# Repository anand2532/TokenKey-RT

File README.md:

# TokenKey RT

TokenKey RT is a compact USB-C desktop/laptop accessory built on the NXP i.MX RT1062 (Cortex-M7, up to 600 MHz; MIMXRT1062DVL6B, 10x10 mm BGA). It accelerates AI token-usage optimization — context reduction, request analysis and cost monitoring — working together with a Linux companion application on the host laptop.

## Repository layout

| Path | Contents |
|------|----------|
| `docs/` | Specifications, design decisions and project documentation |
| `docs/poc/` | Proof-of-concept and product-value analyses (TokenKey PoC bot; used by TokenKey PM) |
| `hardware/schematic/` | Whole KiCad project: `TokenKey-RT.kicad_pro`, `.kicad_sch` (plus sub-sheets), 4-layer `.kicad_pcb` and `.kicad_dru` |
| `hardware/libraries/` | Project symbols, footprints and 3D models |
| `firmware/` | i.MX RT1062 firmware and USB protocol |
| `software/` | Laptop companion application |
| `fab/` | Manufacturing outputs (Gerbers, drill, BOM, pick-and-place, assembly drawings) |

## Documentation

- [Baseline specifications & requirements](docs/baseline-specs.md)
- [Design decisions](docs/decisions.md)

## Contributing

Every change follows the same flow:

1. Open an issue describing the change.
2. Create a branch named `issue-N-short` (e.g. `issue-1-scaffold`).
3. Commit with `Fixes #N` in the commit message.
4. Open a pull request into `main`.
5. Merge the PR, which closes the issue.

No direct pushes to `main`, and no force-pushes.

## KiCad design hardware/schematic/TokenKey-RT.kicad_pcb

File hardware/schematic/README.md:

# hardware/schematic

The whole KiCad project for the TokenKey RT board lives here: `TokenKey-RT.kicad_pro`, `TokenKey-RT.kicad_sch` (plus sub-sheets), the 4-layer `TokenKey-RT.kicad_pcb` and `TokenKey-RT.kicad_dru`. KiCad only links the `.kicad_sch` and `.kicad_pcb` that sit next to the `.kicad_pro`, so keep them together in this folder.

## Deprecated generators (issue #26)

`tools/gen.py` and `tools/gen_pinmap.py` are kept for history only and refuse to run. The schematic is the source of truth and is edited directly in KiCad; re-running `gen.py` would overwrite hand edits such as L2 (#24) and the J2 header (#44). `docs/pin-map.md` is a frozen snapshot: update it by hand with any pin-mux change. `tools/rt1062_10x10_balls.json` stays as ball-function reference data.

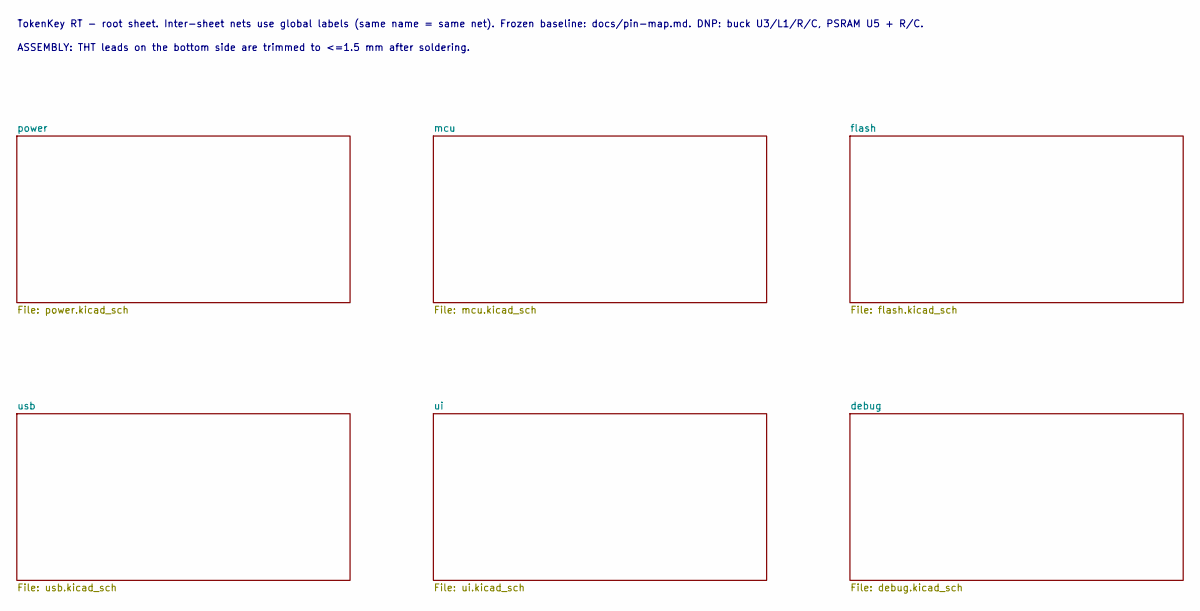
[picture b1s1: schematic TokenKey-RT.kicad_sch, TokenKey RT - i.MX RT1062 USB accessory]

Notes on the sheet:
TokenKey RT - root sheet. Inter-sheet nets use global labels (same name = same net). Frozen baseline: docs/pin-map.md. DNP: buck U3/L1/R/C, PSRAM U5 + R/C.
ASSEMBLY: THT leads on the bottom side are trimmed to <=1.5 mm after soldering.

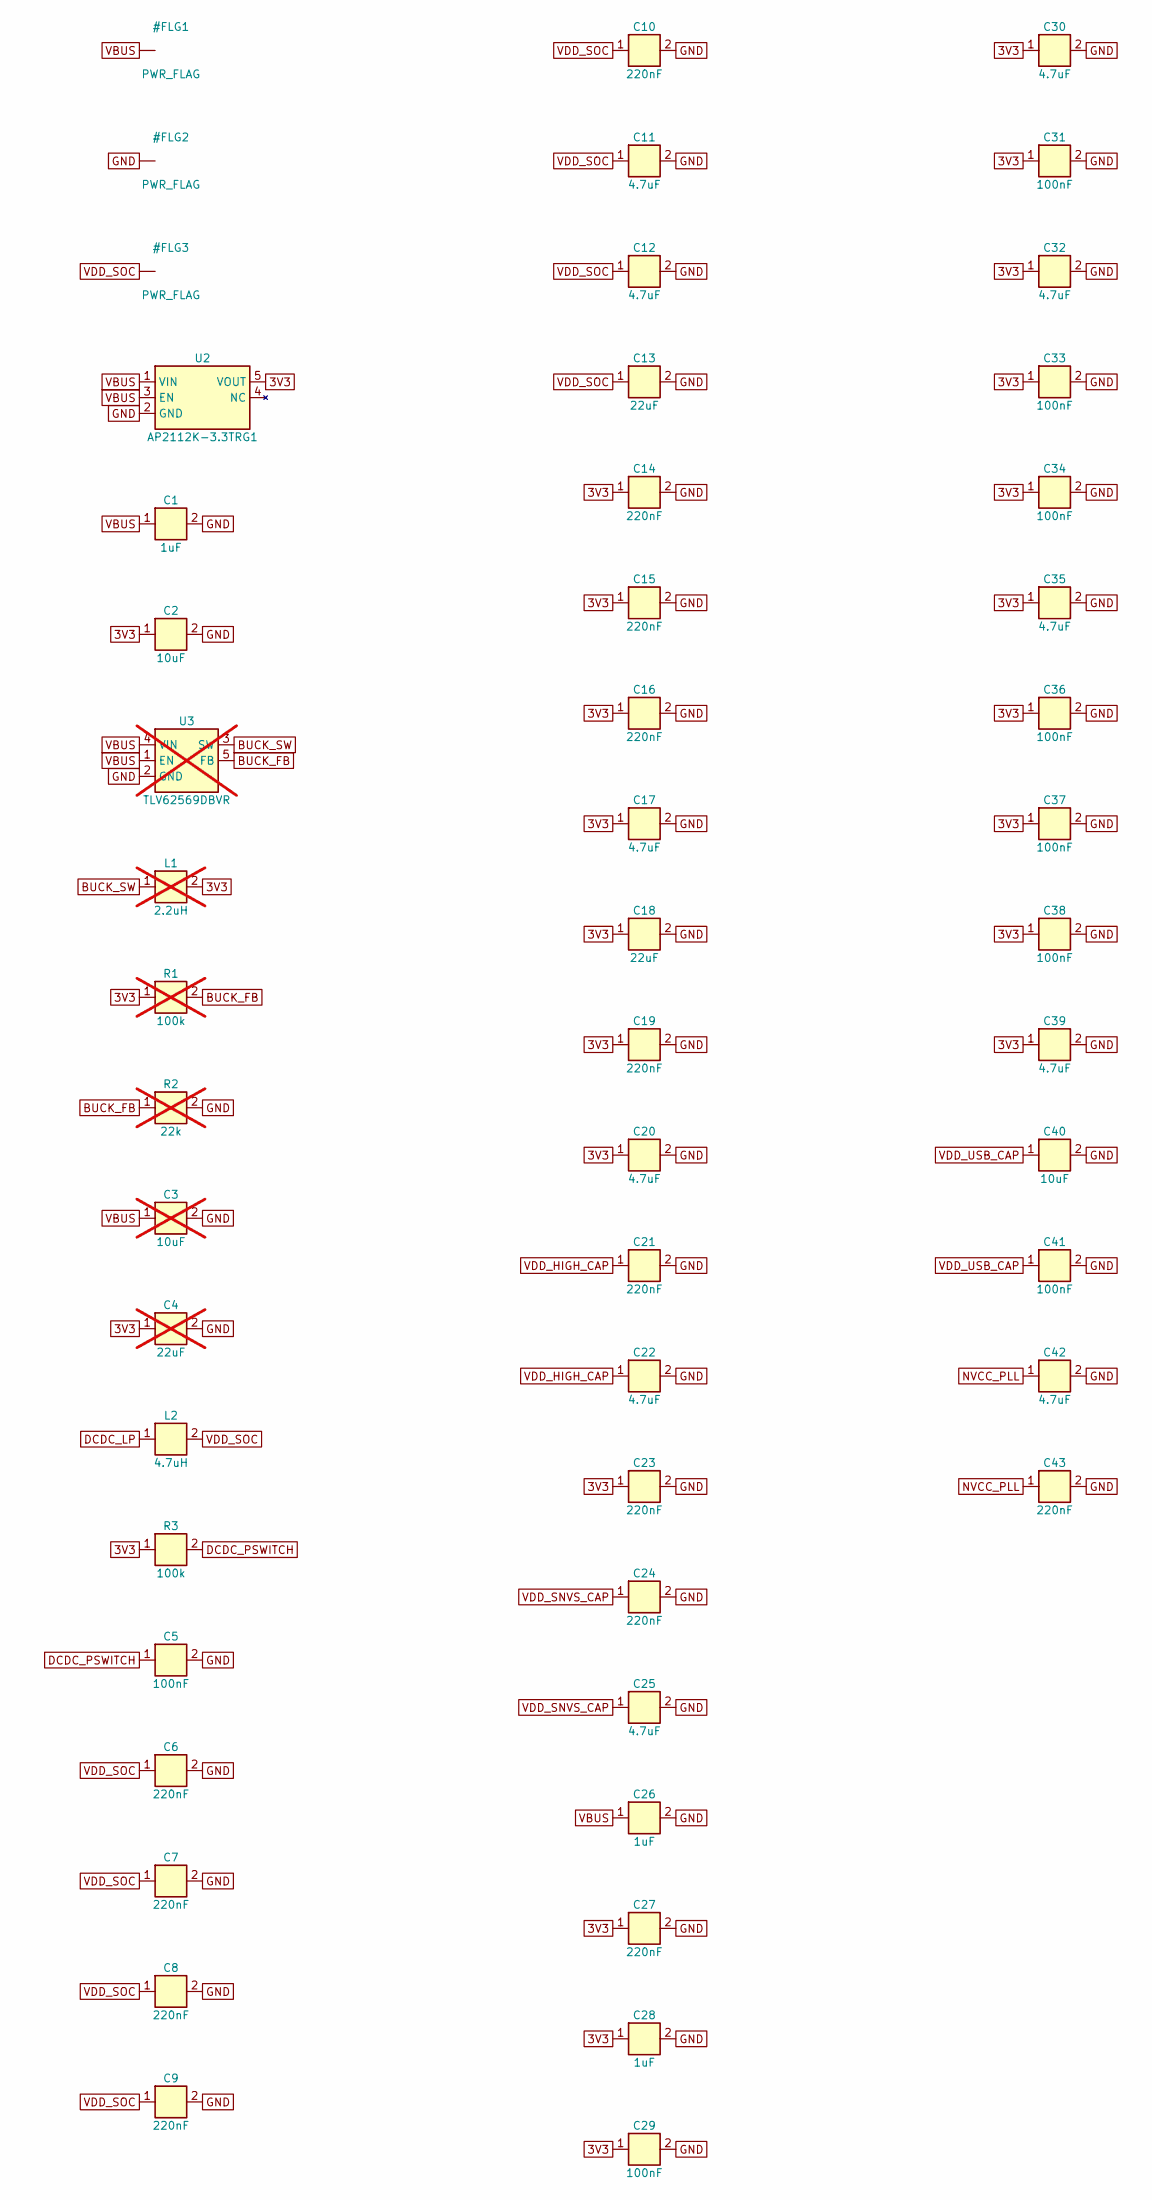
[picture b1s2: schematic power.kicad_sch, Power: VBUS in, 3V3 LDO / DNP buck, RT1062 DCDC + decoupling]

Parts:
C1, C26, C28: 1uF; C_0402_1005Metric; MPN CL05A105KA5NQNC; LCSC C52923
C2, C40: 10uF; C_0603_1608Metric; MPN CL10A106KP8NNNC; LCSC C19702
C3: 10uF; C_0603_1608Metric; MPN CL10A106KP8NNNC; LCSC C19702; not fitted
C4: 22uF; C_0603_1608Metric; MPN CL10A226MQ8NRNC; LCSC C59461; not fitted
C5, C29, C31, C33, C34, C36, C37, C38, C41: 100nF; C_0402_1005Metric; MPN CL05B104KO5NNNC; LCSC C1525
C6, C7, C8, C9, C10, C14, C15, C16, C19, C21, C23, C24, C27, C43: 220nF; C_0402_1005Metric; MPN CL05A224KA5NNNC; LCSC C47129
C11, C12, C17, C20, C22, C25, C30, C32, C35, C39, C42: 4.7uF; C_0402_1005Metric; MPN CL05A475MP5NRNC; LCSC C23733
C13, C18: 22uF; C_0603_1608Metric; MPN CL10A226MQ8NRNC; LCSC C59461
L1: 2.2uH; L_Sunlord_SWPA4020S; MPN SWPA4020S2R2MT; LCSC C83423; not fitted
L2: 4.7uH; L_3.0x3.0mm_TDK_VLS3015CX; MPN VLS3015CX-4R7M-1; LCSC C3220938
R1: 100k; R_0402_1005Metric; MPN 0402WGF1003TCE; LCSC C25741; not fitted
R2: 22k; R_0402_1005Metric; MPN 0402WGF2202TCE; LCSC C25768; not fitted
R3: 100k; R_0402_1005Metric; MPN 0402WGF1003TCE; LCSC C25741
U2: AP2112K-3.3TRG1; SOT-23-5; MPN AP2112K-3.3TRG1; LCSC C51118
U3: TLV62569DBVR; SOT-23-5; MPN TLV62569DBVR; LCSC C141836; not fitted

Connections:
3V3: C2.1, C4.1, C14.1, C15.1, C16.1, C17.1, C18.1, C19.1, C20.1, C23.1, C27.1, C28.1, C29.1, C30.1, C31.1, C32.1, C33.1, C34.1, C35.1, C36.1, C37.1, C38.1, C39.1, L1.2, R1.1, R3.1, U2.5 (VOUT); also elsewhere on the board
BUCK_FB: R1.2, R2.1, U3.5 (FB)
BUCK_SW: L1.1, U3.3 (SW)
DCDC_LP: L2.1; also elsewhere on the board
DCDC_PSWITCH: C5.1, R3.2; also elsewhere on the board
GND: C1.2, C2.2, C3.2, C4.2, C5.2, C6.2, C7.2, C8.2, C9.2, C10.2, C11.2, C12.2, C13.2, C14.2, C15.2, C16.2, C17.2, C18.2, C19.2, C20.2, C21.2, C22.2, C23.2, C24.2, C25.2, C26.2, C27.2, C28.2, C29.2, C30.2, C31.2, C32.2, C33.2, C34.2, C35.2, C36.2, C37.2, C38.2, C39.2, C40.2, C41.2, C42.2, C43.2, R2.2, U2.2 (GND), U3.2 (GND); also elsewhere on the board
NVCC_PLL: C42.1, C43.1; also elsewhere on the board
VBUS: C1.1, C3.1, C26.1, U2.1 (VIN), U2.3 (EN), U3.1 (EN), U3.4 (VIN); also elsewhere on the board
VDD_HIGH_CAP: C21.1, C22.1; also elsewhere on the board
VDD_SNVS_CAP: C24.1, C25.1; also elsewhere on the board
VDD_SOC: C6.1, C7.1, C8.1, C9.1, C10.1, C11.1, C12.1, C13.1, L2.2; also elsewhere on the board
VDD_USB_CAP: C40.1, C41.1; also elsewhere on the board

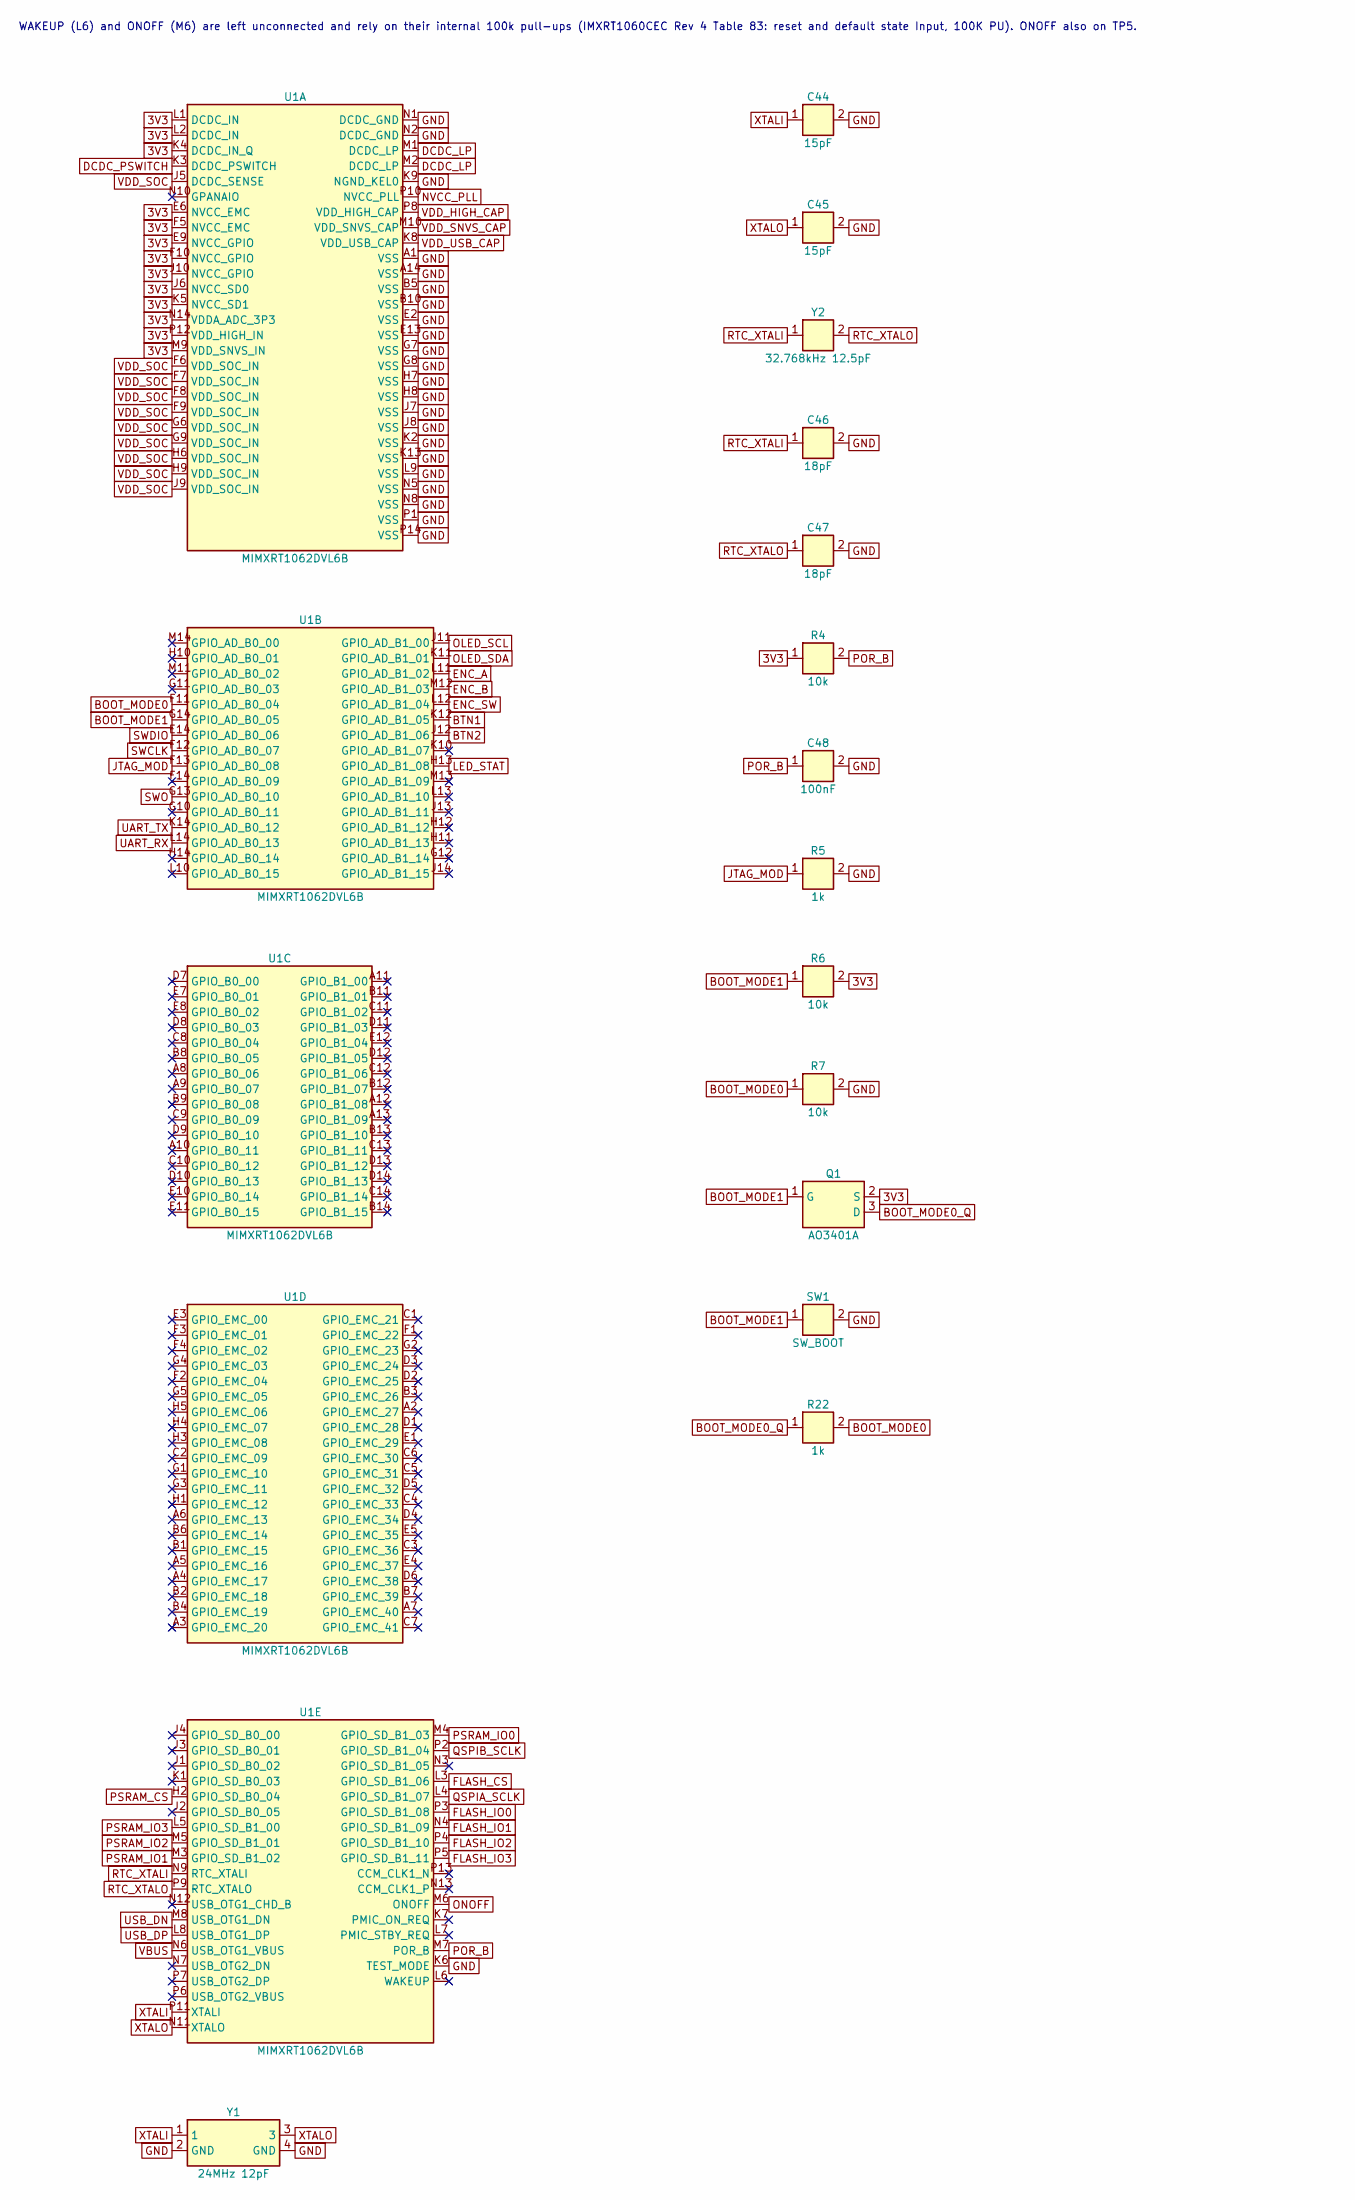
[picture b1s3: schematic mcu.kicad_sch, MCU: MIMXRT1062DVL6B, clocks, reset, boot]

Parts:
C44, C45: 15pF; C_0402_1005Metric; MPN 0402CG150J500NT; LCSC C1548
C46, C47: 18pF; C_0402_1005Metric; MPN 0402CG180J500NT; LCSC C1549
C48: 100nF; C_0402_1005Metric; MPN CL05B104KO5NNNC; LCSC C1525
Q1: AO3401A; SOT-23; MPN AO3401A; LCSC C15127
R4, R6, R7: 10k; R_0402_1005Metric; MPN 0402WGF1002TCE; LCSC C25744
R5, R22: 1k; R_0402_1005Metric; MPN 0402WGF1001TCE; LCSC C11702
SW1: SW_BOOT; SW_SPST_B3U-1000P; MPN B3U-1000P; LCSC C231329
U1: MIMXRT1062DVL6B; NXP_MAPBGA-196_10x10mm_Layout14x14_P0.65mm; MPN MIMXRT1062DVL6B; LCSC C2847497
Y1: 24MHz 12pF; Crystal_SMD_3225-4Pin_3.2x2.5mm; MPN X322524MOB4SI; LCSC C70590
Y2: 32.768kHz 12.5pF; Crystal_SMD_3215-2Pin_3.2x1.5mm; MPN ABS07-32.768KHZ-T; LCSC C130253

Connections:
3V3: Q1.2 (S), R4.1, R6.2, U1.E6 (NVCC_EMC), U1.E9 (NVCC_GPIO), U1.F5 (NVCC_EMC), U1.F10 (NVCC_GPIO), U1.J6 (NVCC_SD0), U1.J10 (NVCC_GPIO), U1.K4 (DCDC_IN_Q), U1.K5 (NVCC_SD1), U1.L1 (DCDC_IN), U1.L2 (DCDC_IN), U1.M9 (VDD_SNVS_IN), U1.N14 (VDDA_ADC_3P3), U1.P12 (VDD_HIGH_IN); also elsewhere on the board
BOOT_MODE0: R7.1, R22.2, U1.F11 (GPIO_AD_B0_04)
BOOT_MODE0_Q: Q1.3 (D), R22.1
BOOT_MODE1: Q1.1 (G), R6.1, SW1.1, U1.G14 (GPIO_AD_B0_05)
BTN1: U1.K12 (GPIO_AD_B1_05); also elsewhere on the board
BTN2: U1.J12 (GPIO_AD_B1_06); also elsewhere on the board
DCDC_LP: U1.M1 (DCDC_LP), U1.M2 (DCDC_LP); also elsewhere on the board
DCDC_PSWITCH: U1.K3 (DCDC_PSWITCH); also elsewhere on the board
ENC_A: U1.L11 (GPIO_AD_B1_02); also elsewhere on the board
ENC_B: U1.M12 (GPIO_AD_B1_03); also elsewhere on the board
ENC_SW: U1.L12 (GPIO_AD_B1_04); also elsewhere on the board
FLASH_CS: U1.L3 (GPIO_SD_B1_06); also elsewhere on the board
FLASH_IO0: U1.P3 (GPIO_SD_B1_08); also elsewhere on the board
FLASH_IO1: U1.N4 (GPIO_SD_B1_09); also elsewhere on the board
FLASH_IO2: U1.P4 (GPIO_SD_B1_10); also elsewhere on the board
FLASH_IO3: U1.P5 (GPIO_SD_B1_11); also elsewhere on the board
GND: C44.2, C45.2, C46.2, C47.2, C48.2, R5.2, R7.2, SW1.2, U1.A1 (VSS), U1.A14 (VSS), U1.B5 (VSS), U1.B10 (VSS), U1.E2 (VSS), U1.E13 (VSS), U1.G7 (VSS), U1.G8 (VSS), U1.H7 (VSS), U1.H8 (VSS), U1.J7 (VSS), U1.J8 (VSS), U1.K2 (VSS), U1.K6 (TEST_MODE), U1.K9 (NGND_KEL0), U1.K13 (VSS), U1.L9 (VSS), U1.N1 (DCDC_GND), U1.N2 (DCDC_GND), U1.N5 (VSS), U1.N8 (VSS), U1.P1 (VSS), U1.P14 (VSS), Y1.2 (GND), Y1.4 (GND); also elsewhere on the board
JTAG_MOD: R5.1, U1.F13 (GPIO_AD_B0_08)
LED_STAT: U1.H13 (GPIO_AD_B1_08); also elsewhere on the board
NVCC_PLL: U1.P10 (NVCC_PLL); also elsewhere on the board
OLED_SCL: U1.J11 (GPIO_AD_B1_00); also elsewhere on the board
OLED_SDA: U1.K11 (GPIO_AD_B1_01); also elsewhere on the board
ONOFF: U1.M6 (ONOFF); also elsewhere on the board
POR_B: C48.1, R4.2, U1.M7 (POR_B); also elsewhere on the board
PSRAM_CS: U1.H2 (GPIO_SD_B0_04); also elsewhere on the board
PSRAM_IO0: U1.M4 (GPIO_SD_B1_03); also elsewhere on the board
PSRAM_IO1: U1.M3 (GPIO_SD_B1_02); also elsewhere on the board
PSRAM_IO2: U1.M5 (GPIO_SD_B1_01); also elsewhere on the board
PSRAM_IO3: U1.L5 (GPIO_SD_B1_00); also elsewhere on the board
QSPIA_SCLK: U1.L4 (GPIO_SD_B1_07); also elsewhere on the board
QSPIB_SCLK: U1.P2 (GPIO_SD_B1_04); also elsewhere on the board
RTC_XTALI: C46.1, U1.N9 (RTC_XTALI), Y2.1
RTC_XTALO: C47.1, U1.P9 (RTC_XTALO), Y2.2
SWCLK: U1.F12 (GPIO_AD_B0_07); also elsewhere on the board
SWDIO: U1.E14 (GPIO_AD_B0_06); also elsewhere on the board
SWO: U1.G13 (GPIO_AD_B0_10); also elsewhere on the board
UART_RX: U1.L14 (GPIO_AD_B0_13); also elsewhere on the board
UART_TX: U1.K14 (GPIO_AD_B0_12); also elsewhere on the board
USB_DN: U1.M8 (USB_OTG1_DN); also elsewhere on the board
USB_DP: U1.L8 (USB_OTG1_DP); also elsewhere on the board
VBUS: U1.N6 (USB_OTG1_VBUS); also elsewhere on the board
VDD_HIGH_CAP: U1.P8 (VDD_HIGH_CAP); also elsewhere on the board
VDD_SNVS_CAP: U1.M10 (VDD_SNVS_CAP); also elsewhere on the board
VDD_SOC: U1.F6 (VDD_SOC_IN), U1.F7 (VDD_SOC_IN), U1.F8 (VDD_SOC_IN), U1.F9 (VDD_SOC_IN), U1.G6 (VDD_SOC_IN), U1.G9 (VDD_SOC_IN), U1.H6 (VDD_SOC_IN), U1.H9 (VDD_SOC_IN), U1.J5 (DCDC_SENSE), U1.J9 (VDD_SOC_IN); also elsewhere on the board
VDD_USB_CAP: U1.K8 (VDD_USB_CAP); also elsewhere on the board
XTALI: C44.1, U1.P11 (XTALI), Y1.1
XTALO: C45.1, U1.N11 (XTALO), Y1.3

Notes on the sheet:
WAKEUP (L6) and ONOFF (M6) are left unconnected and rely on their internal 100k pull-ups (IMXRT1060CEC Rev 4 Table 83: reset and default state Input, 100K PU). ONOFF also on TP5.

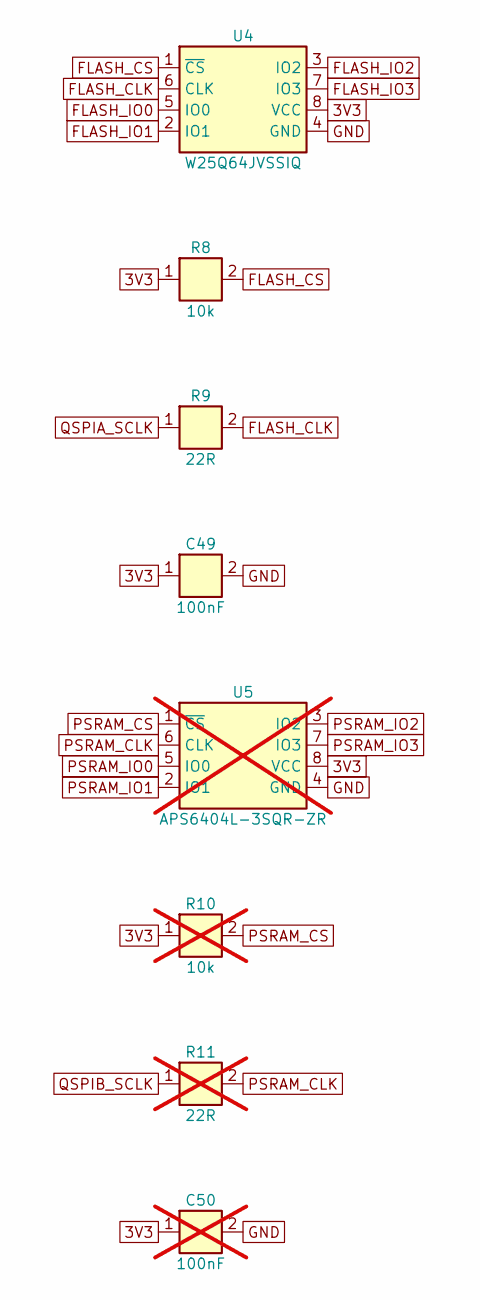
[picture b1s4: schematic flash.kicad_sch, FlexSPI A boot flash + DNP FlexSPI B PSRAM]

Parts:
C49: 100nF; C_0402_1005Metric; MPN CL05B104KO5NNNC; LCSC C1525
C50: 100nF; C_0402_1005Metric; MPN CL05B104KO5NNNC; LCSC C1525; not fitted
R8: 10k; R_0402_1005Metric; MPN 0402WGF1002TCE; LCSC C25744
R9: 22R; R_0402_1005Metric; MPN 0402WGF220JTCE; LCSC C25092
R10: 10k; R_0402_1005Metric; MPN 0402WGF1002TCE; LCSC C25744; not fitted
R11: 22R; R_0402_1005Metric; MPN 0402WGF220JTCE; LCSC C25092; not fitted
U4: W25Q64JVSSIQ; SOIC-8_5.3x5.3mm_P1.27mm; MPN W25Q64JVSSIQ; LCSC C179171
U5: APS6404L-3SQR-ZR; Winbond_USON-8-1EP_3x2mm_P0.5mm_EP0.2x1.6mm; MPN APS6404L-3SQR-ZR; LCSC C3040877; not fitted

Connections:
3V3: C49.1, C50.1, R8.1, R10.1, U4.8 (VCC), U5.8 (VCC); also elsewhere on the board
FLASH_CLK: R9.2, U4.6 (CLK)
FLASH_CS: R8.2, U4.1 (~CS); also elsewhere on the board
FLASH_IO0: U4.5 (IO0); also elsewhere on the board
FLASH_IO1: U4.2 (IO1); also elsewhere on the board
FLASH_IO2: U4.3 (IO2); also elsewhere on the board
FLASH_IO3: U4.7 (IO3); also elsewhere on the board
GND: C49.2, C50.2, U4.4 (GND), U5.4 (GND); also elsewhere on the board
PSRAM_CLK: R11.2, U5.6 (CLK)
PSRAM_CS: R10.2, U5.1 (~CS); also elsewhere on the board
PSRAM_IO0: U5.5 (IO0); also elsewhere on the board
PSRAM_IO1: U5.2 (IO1); also elsewhere on the board
PSRAM_IO2: U5.3 (IO2); also elsewhere on the board
PSRAM_IO3: U5.7 (IO3); also elsewhere on the board
QSPIA_SCLK: R9.1; also elsewhere on the board
QSPIB_SCLK: R11.1; also elsewhere on the board

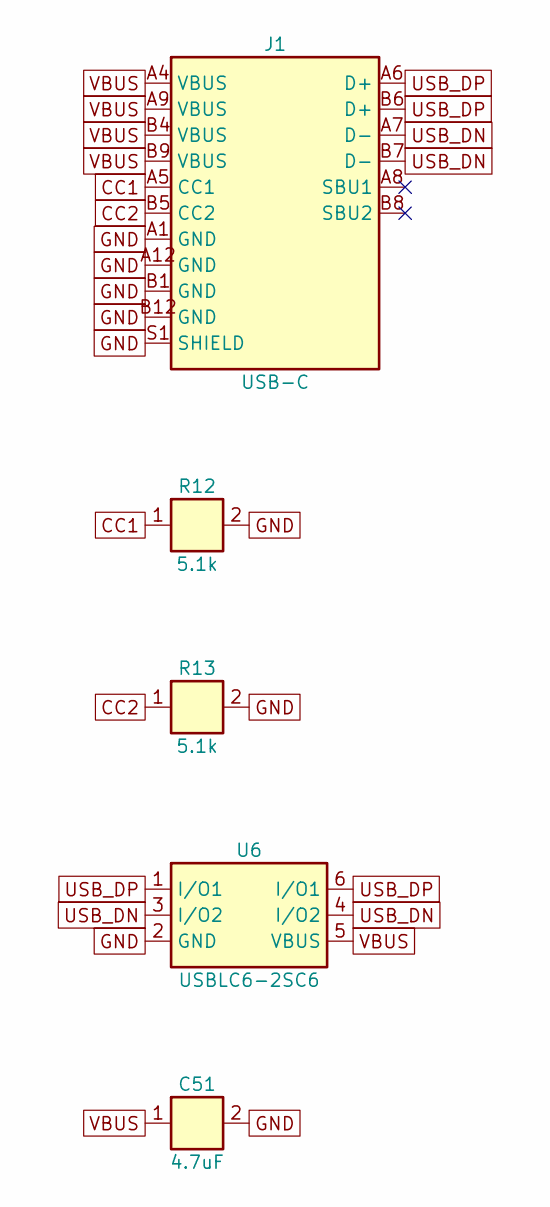
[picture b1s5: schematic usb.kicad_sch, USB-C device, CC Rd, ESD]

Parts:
C51: 4.7uF; C_0402_1005Metric; MPN CL05A475MP5NRNC; LCSC C23733
J1: USB-C; USB_C_Receptacle_HRO_TYPE-C-31-M-12; MPN TYPE-C-31-M-12; LCSC C165948
R12, R13: 5.1k; R_0402_1005Metric; MPN 0402WGF5101TCE; LCSC C25905
U6: USBLC6-2SC6; SOT-23-6; MPN USBLC6-2SC6; LCSC C7519

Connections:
CC1: J1.A5 (CC1), R12.1
CC2: J1.B5 (CC2), R13.1
GND: C51.2, J1.A1 (GND), J1.A12 (GND), J1.B1 (GND), J1.B12 (GND), J1.S1 (SHIELD), R12.2, R13.2, U6.2 (GND); also elsewhere on the board
USB_DN: J1.A7 (D-), J1.B7 (D-), U6.3 (I/O2), U6.4 (I/O2); also elsewhere on the board
USB_DP: J1.A6 (D+), J1.B6 (D+), U6.1 (I/O1), U6.6 (I/O1); also elsewhere on the board
VBUS: C51.1, J1.A4 (VBUS), J1.A9 (VBUS), J1.B4 (VBUS), J1.B9 (VBUS), U6.5 (VBUS); also elsewhere on the board

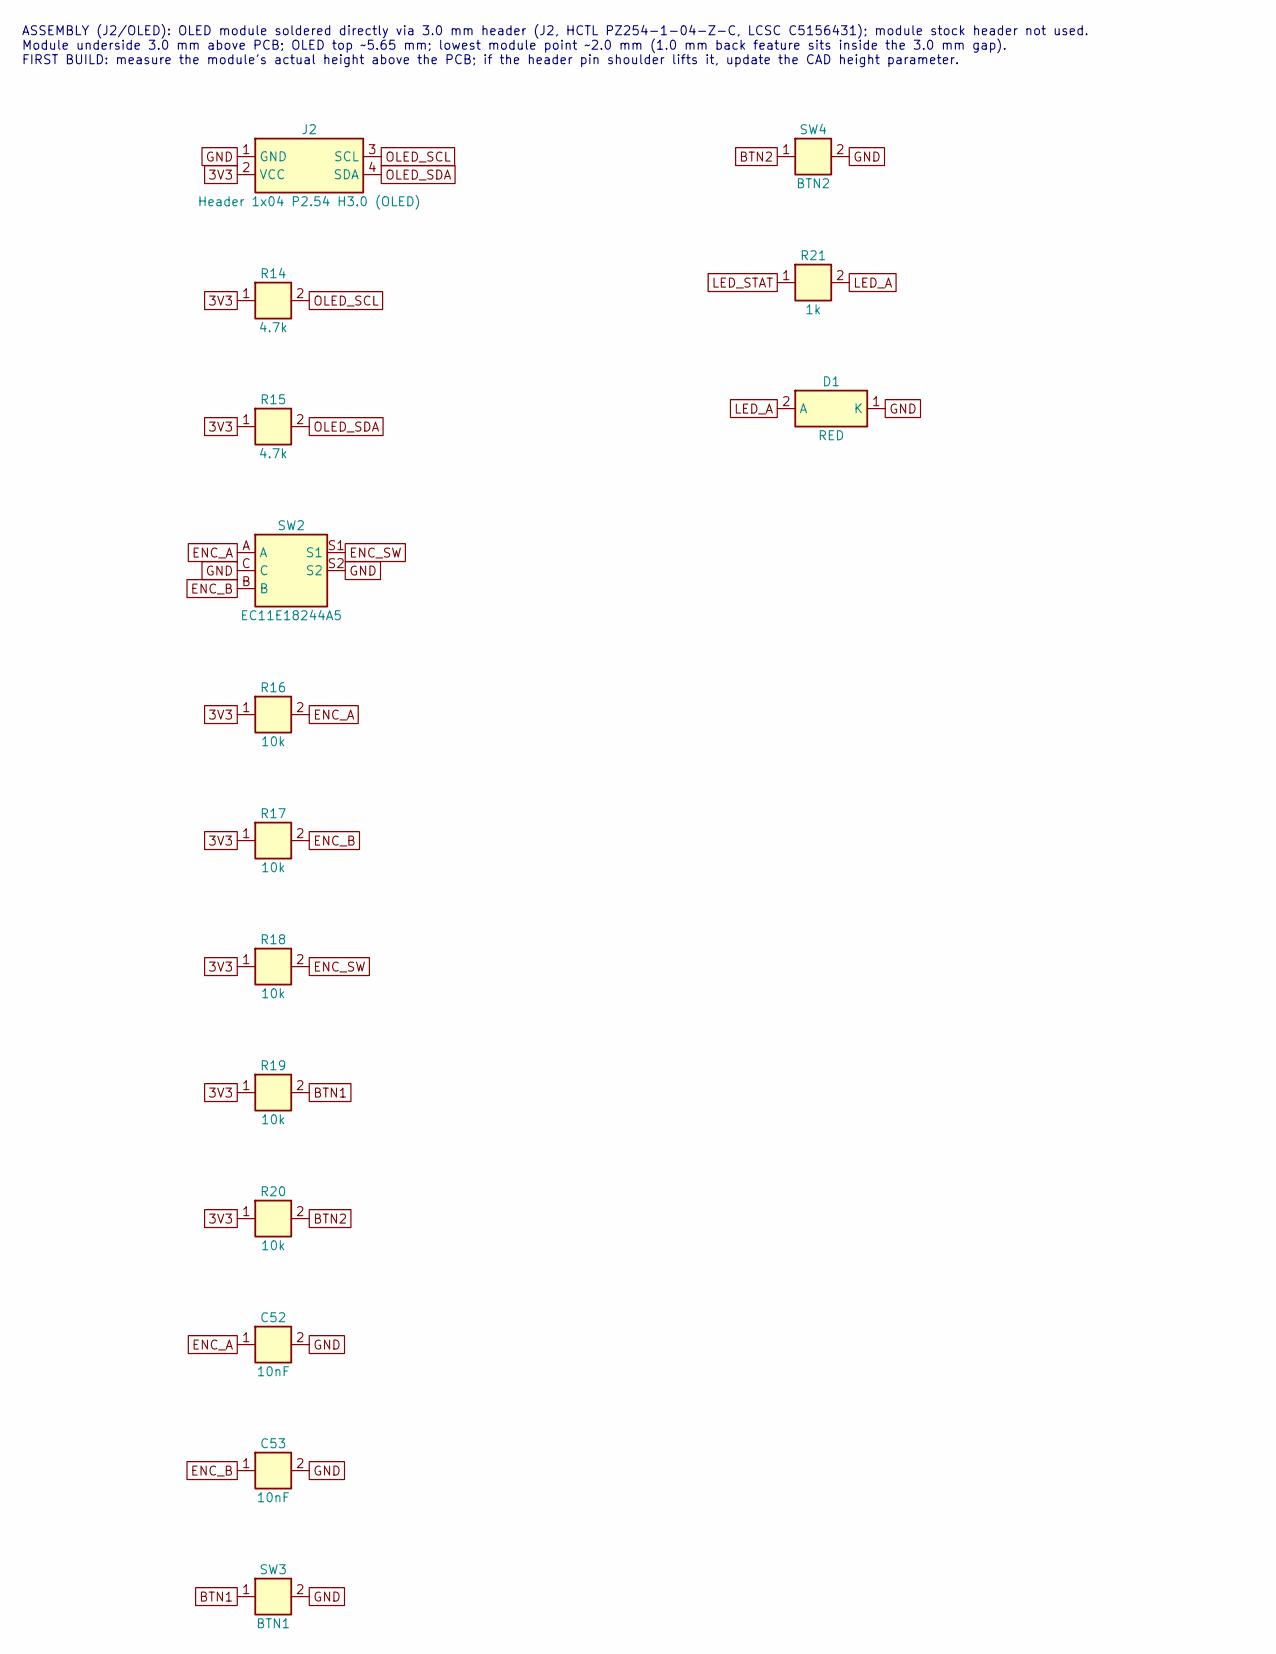
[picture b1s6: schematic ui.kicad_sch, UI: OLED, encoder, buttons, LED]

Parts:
C52, C53: 10nF; C_0402_1005Metric; MPN CL05B103KB5NNNC; LCSC C15195
D1: RED; LED_0603_1608Metric; MPN KT-0603R; LCSC C2286
J2: Header 1x04 P2.54 H3.0 (OLED); PinHeader_1x04_P2.54mm_Vertical; MPN PZ254-1-04-Z-C; LCSC C5156431
R14, R15: 4.7k; R_0402_1005Metric; MPN 0402WGF4701TCE; LCSC C25900
R16, R17, R18, R19, R20: 10k; R_0402_1005Metric; MPN 0402WGF1002TCE; LCSC C25744
R21: 1k; R_0402_1005Metric; MPN 0402WGF1001TCE; LCSC C11702
SW2: EC11E18244A5; RotaryEncoder_Alps_EC11E-Switch_Vertical_H20mm; MPN EC11E18244A5; LCSC C255515
SW3: BTN1; SW_SPST_B3U-1000P; MPN B3U-1000P; LCSC C231329
SW4: BTN2; SW_SPST_B3U-1000P; MPN B3U-1000P; LCSC C231329

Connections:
3V3: J2.2 (VCC), R14.1, R15.1, R16.1, R17.1, R18.1, R19.1, R20.1; also elsewhere on the board
BTN1: R19.2, SW3.1; also elsewhere on the board
BTN2: R20.2, SW4.1; also elsewhere on the board
ENC_A: C52.1, R16.2, SW2.A; also elsewhere on the board
ENC_B: C53.1, R17.2, SW2.B; also elsewhere on the board
ENC_SW: R18.2, SW2.S1; also elsewhere on the board
GND: C52.2, C53.2, D1.1 (K), J2.1 (GND), SW2.C, SW2.S2, SW3.2, SW4.2; also elsewhere on the board
LED_A: D1.2 (A), R21.2
LED_STAT: R21.1; also elsewhere on the board
OLED_SCL: J2.3 (SCL), R14.2; also elsewhere on the board
OLED_SDA: J2.4 (SDA), R15.2; also elsewhere on the board

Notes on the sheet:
ASSEMBLY (J2/OLED): OLED module soldered directly via 3.0 mm header (J2, HCTL PZ254-1-04-Z-C, LCSC C5156431); module stock header not used. Module underside 3.0 mm above PCB; OLED top ~5.65 mm; lowest module point ~2.0 mm (1.0 mm back feature sits inside the 3.0 mm gap). FIRST BUILD: measure the mo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

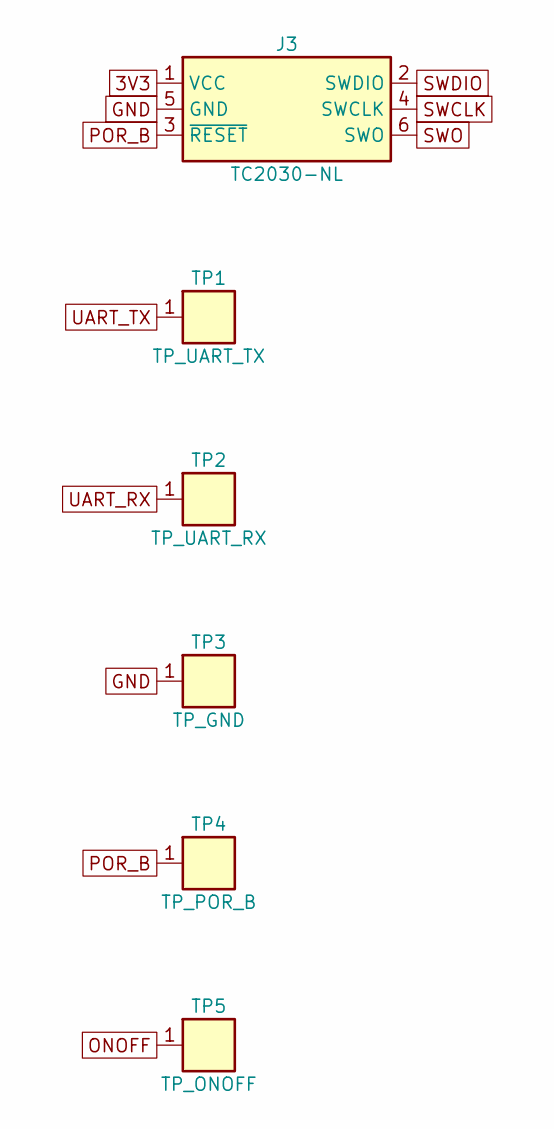
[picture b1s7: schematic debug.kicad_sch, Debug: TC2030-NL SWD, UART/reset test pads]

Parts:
J3: TC2030-NL; Tag-Connect_TC2030-IDC-NL_2x03_P1.27mm_Vertical; MPN N/A - footprint only; LCSC N/A - footprint only
TP1: TP_UART_TX; TestPoint_Pad_D1.0mm; MPN N/A - footprint only; LCSC N/A - footprint only
TP2: TP_UART_RX; TestPoint_Pad_D1.0mm; MPN N/A - footprint only; LCSC N/A - footprint only
TP3: TP_GND; TestPoint_Pad_D1.0mm; MPN N/A - footprint only; LCSC N/A - footprint only
TP4: TP_POR_B; TestPoint_Pad_D1.0mm; MPN N/A - footprint only; LCSC N/A - footprint only
TP5: TP_ONOFF; TestPoint_Pad_D1.0mm; MPN N/A - footprint only; LCSC N/A - footprint only

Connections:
3V3: J3.1 (VCC); also elsewhere on the board
GND: J3.5 (GND), TP3.1; also elsewhere on the board
ONOFF: TP5.1; also elsewhere on the board
POR_B: J3.3 (~RESET), TP4.1; also elsewhere on the board
SWCLK: J3.4 (SWCLK); also elsewhere on the board
SWDIO: J3.2 (SWDIO); also elsewhere on the board
SWO: J3.6 (SWO); also elsewhere on the board
UART_RX: TP2.1; also elsewhere on the board
UART_TX: TP1.1; also elsewhere on the board

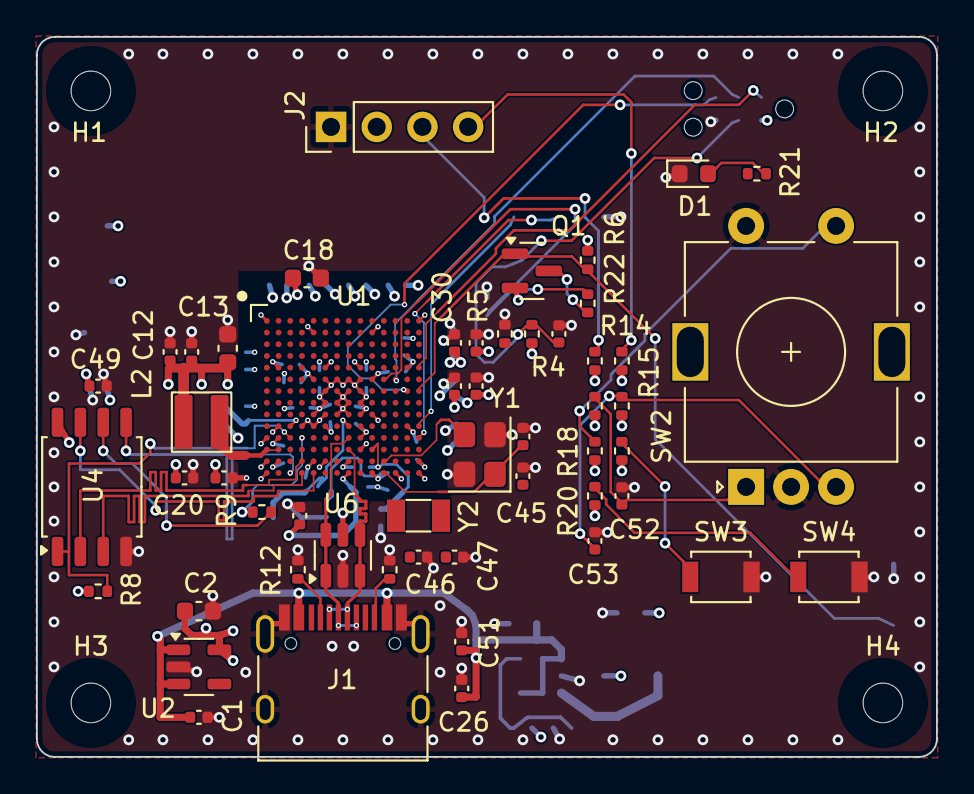
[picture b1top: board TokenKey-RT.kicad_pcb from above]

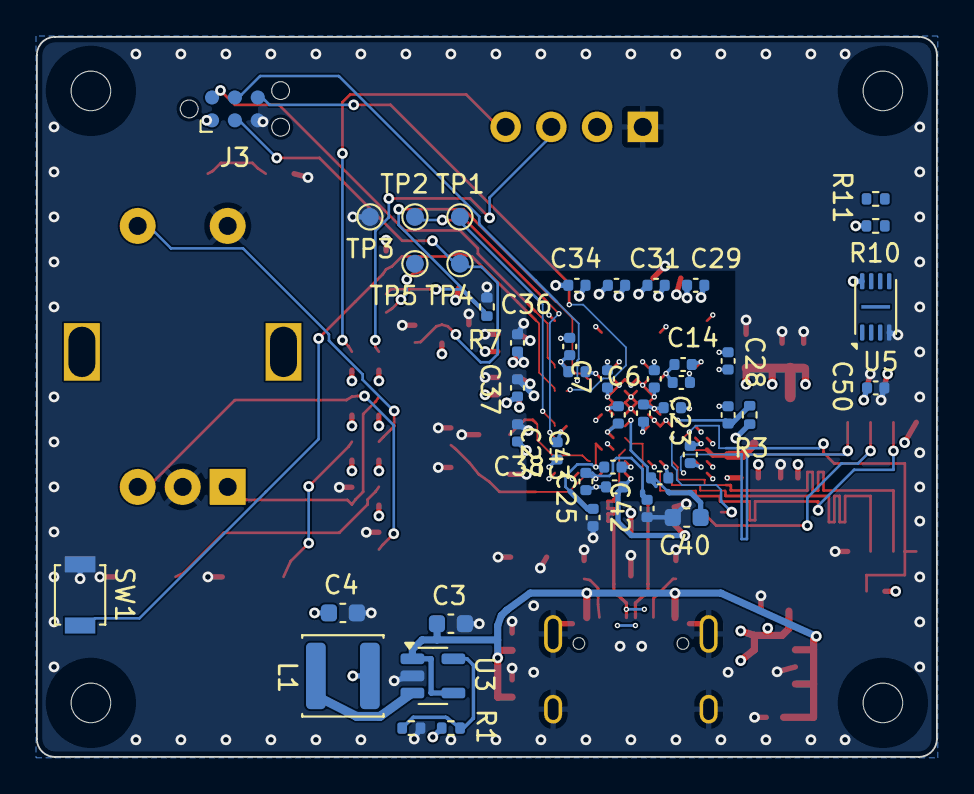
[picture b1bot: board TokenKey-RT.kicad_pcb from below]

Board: 4 copper layers, 50.0 x 40.0 mm, 103 parts (46 on the bottom side), 54 nets.

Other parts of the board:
H1, H2, H3, H4: M2; MountingHole_2.2mm_M2

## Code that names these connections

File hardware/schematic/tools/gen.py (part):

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
# ---- MCU pin assignment (frozen baseline; LED moved K10 -> H13)
PIN = {
 'GPIO_SD_B1_06': 'FLASH_CS', 'GPIO_SD_B1_07': 'QSPIA_SCLK', 'GPIO_SD_B1_08': 'FLASH_IO0', 'GPIO_SD_B1_09': 'FLASH_IO1',
 'GPIO_SD_B1_10': 'FLASH_IO2', 'GPIO_SD_B1_11': 'FLASH_IO3',
 'GPIO_SD_B1_00': 'PSRAM_IO3', 'GPIO_SD_B1_01': 'PSRAM_IO2', 'GPIO_SD_B1_02': 'PSRAM_IO1', 'GPIO_SD_B1_03': 'PSRAM_IO0',
 'GPIO_SD_B1_04': 'QSPIB_SCLK', 'GPIO_SD_B0_04': 'PSRAM_CS',
 'USB_OTG1_DP': 'USB_DP', 'USB_OTG1_DN': 'USB_DN', 'USB_OTG1_VBUS': 'VBUS',
 'XTALI': 'XTALI', 'XTALO': 'XTALO', 'RTC_XTALI': 'RTC_XTALI', 'RTC_XTALO': 'RTC_XTALO',
 'GPIO_AD_B0_04': 'BOOT_MODE0', 'GPIO_AD_B0_05': 'BOOT_MODE1', 'POR_B': 'POR_B', 'ONOFF': 'ONOFF', 'TEST_MODE': 'GND',
 'GPIO_AD_B0_06': 'SWDIO', 'GPIO_AD_B0_07': 'SWCLK', 'GPIO_AD_B0_10': 'SWO', 'GPIO_AD_B0_08': 'JTAG_MOD',
 'GPIO_AD_B0_12': 'UART_TX', 'GPIO_AD_B0_13': 'UART_RX',
 'GPIO_AD_B1_00': 'OLED_SCL', 'GPIO_AD_B1_01': 'OLED_SDA', 'GPIO_AD_B1_02': 'ENC_A', 'GPIO_AD_B1_03': 'ENC_B',
 'GPIO_AD_B1_04': 'ENC_SW', 'GPIO_AD_B1_05': 'BTN1', 'GPIO_AD_B1_06': 'BTN2', 'GPIO_AD_B1_08': 'LED_STAT',
}
SUPNET = {'VSS': 'GND', 'DCDC_GND': 'GND', 'NGND_KEL0': 'GND', 'DCDC_IN': '3V3', 'DCDC_IN_Q': '3V3', 'VDD_HIGH_IN': '3V3',
          'VDD_SNVS_IN': '3V3', 'NVCC_EMC': '3V3', 'NVCC_GPIO': '3V3', 'NVCC_SD0': '3V3', 'NVCC_SD1': '3V3', 'VDDA_ADC_3P3': '3V3',
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
# ---- debug
part('debug', nref('J'), 'TC2030_SWD', 'TC2030-NL', 'Connector:Tag-Connect_TC2030-IDC-NL_2x03_P1.27mm_Vertical', 'N/A - footprint only', 'N/A - footprint only',
     {'1': '3V3', '5': 'GND', '3': 'POR_B', '2': 'SWDIO', '4': 'SWCLK', '6': 'SWO'}, note='Tag-Connect TC2030-CTX mapping',
     extra=FP_ONLY)
for n in ['UART_TX', 'UART_RX', 'GND', 'POR_B', 'ONOFF']:
    part('debug', nref('TP'), 'TestPoint', 'TP_' + n, FP['TP'], 'N/A - footprint only', 'N/A - footprint only', {'1': n}, note='Bare copper test pad', extra=FP_ONLY)
# R_S added in PM review; numbered last so existing references do not shift
R('mcu', '1k', 'BOOT_MODE0_Q', 'BOOT_MODE0', note='R_S: series 1k Q1 drain -> BOOT_MODE0 (F11); limits current if F11 is driven as GPIO. Q1 on: BM0 = 3.3*10k/11k = 3.0 V')

# ---------------------------------------------------------------- symbol lib text
def unit_geom(pins, hide_names):
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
